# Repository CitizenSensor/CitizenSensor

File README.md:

# CitizenSensor Nitrate Measurement System

This repository contains all design files for the CitizenSensor nitrate measuring system.

## Repository Layout

```
+ 1_RaspberryPi-HAT/            Raspberry Pi HAT allowing electro-chemical measurements
| + Firmware/                   firmware for the ADuCM350 on the HAT
| + Hardware/                   PCB design files for the HAT
+ 2_Software/                   Main software running on the Raspberry Pi
+ 3_Electrometer/               PCB design files for the electrometer amplifier
+ 4_ConnectorBoard/             PCB design files for a small board to connect further components
+ 5_Enclosure/                  3D printable enclosure
+ 6_Accessories/                Additional helpful items
+ README.md                     this readme
```

## Documentation

Documentation can be found in the [CitizenSensor Wiki](https://github.com/CitizenSensor/CitizenSensor/wiki)

## Known Issues

See [Open Issues](https://github.com/CitizenSensor/CitizenSensor/issues?utf8=%E2%9C%93&q=is%3Aopen+is%3Aissue).

## License

The hardware documentation is licensed under CERN OHL v.1.2.

Software is licensed under GPLv3.

For details see licensing info in the respective sub directories.

---

Copyright FabLab München e.V. and Fraunhofer EMFT 2019-2020

CitizenSensor is sponsored by the Federal Ministry of Education and Research

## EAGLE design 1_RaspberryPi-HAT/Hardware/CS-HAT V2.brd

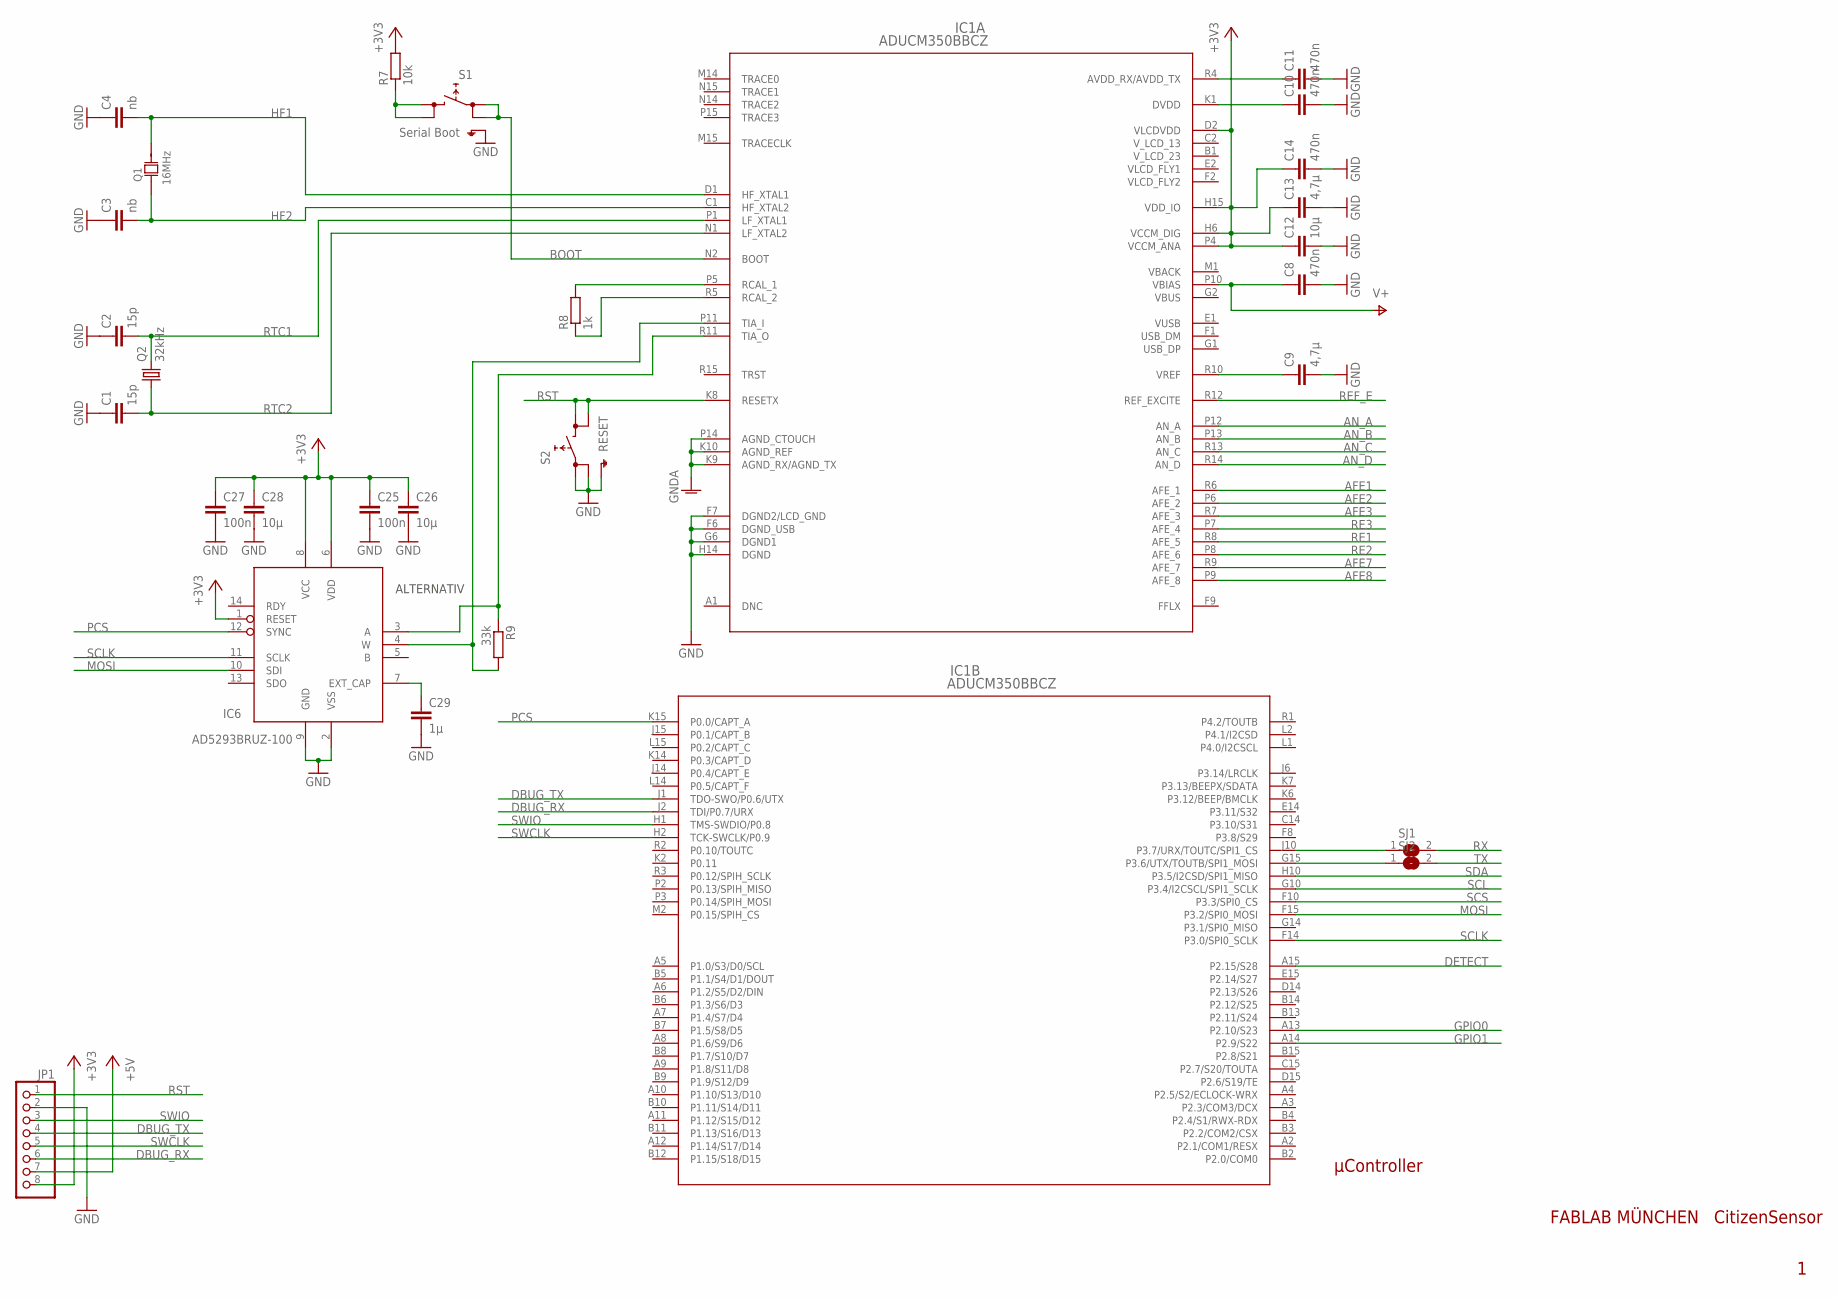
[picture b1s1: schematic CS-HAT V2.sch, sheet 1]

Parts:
C1, C2: 15p; C0805
C3, C4: nb; C0805
C8, C10, C11, C14: 470n; C0805
C9, C13: 4,7µ; C1206
C12, C26, C28: 10µ; C1206
C25, C27: 100n; C0805
C29: 1µ; C1206
IC1: ADUCM350BBCZ; BC_120_3
IC6: AD5293BRUZ-100; TSSOP14
JP1: PINHD-1X8S; 1X08S
Q1: 16MHz; JXS53
Q2: 32kHz; FC-12M
R7: 10k; R0805
R8: 1k; R0805
R9: 33k; R0805
S1: Serial Boot; SKHMPXE010
S2: RESET; SKHMPXE010
SJ1, SJ2: SJ

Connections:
+3V3: C12.1, C13.1, C14.1, C25.1, C26.1, C27.1, C28.1, IC1.D2 (VLCDVDD), IC1.H6 (VCCM_DIG), IC1.H15 (VDD_IO), IC1.P4 (VCCM_ANA), IC6.1 (RESET), IC6.6 (VDD), IC6.8 (VCC), JP1.8, R7.2; also elsewhere on the board
+5V: JP1.7; also elsewhere on the board
AFE1: IC1.R6 (AFE_1); also elsewhere on the board
AFE2: IC1.P6 (AFE_2)
AFE3: IC1.R7 (AFE_3); also elsewhere on the board
AFE7: IC1.R9 (AFE_7); also elsewhere on the board
AFE8: IC1.P9 (AFE_8); also elsewhere on the board
AN_A: IC1.P12 (AN_A); also elsewhere on the board
AN_B: IC1.P13 (AN_B)
AN_C: IC1.R13 (AN_C)
AN_D: IC1.R14 (AN_D); also elsewhere on the board
BOOT: IC1.N2 (BOOT), S1.1 (1.1), S1.2 (1.2); also elsewhere on the board
DBUG_RX: IC1.J2 (TDI/P0.7/URX), JP1.6
DBUG_TX: IC1.J1 (TDO-SWO/P0.6/UTX), JP1.4
DETECT: IC1.A15 (P2.15/S28); also elsewhere on the board
GND: C1.1, C2.1, C3.1, C4.1, C8.2, C9.2, C10.2, C11.2, C12.2, C13.2, C14.2, C25.2, C26.2, C27.2, C28.2, C29.2, IC1.F6 (DGND_USB), IC1.F7 (DGND2/LCD_GND), IC1.G6 (DGND1), IC1.H14 (DGND), IC6.2 (VSS), IC6.9 (GND), JP1.2, S1.5 (SH), S2.1 (1.1), S2.2 (1.2), S2.5 (SH); also elsewhere on the board
GNDA: IC1.K9 (AGND_RX/AGND_TX), IC1.K10 (AGND_REF), IC1.P14 (AGND_CTOUCH); also elsewhere on the board
GPIO0: IC1.A13 (P2.10/S23); also elsewhere on the board
GPIO1: IC1.A14 (P2.9/S22); also elsewhere on the board
HF1: C4.2, IC1.D1 (HF_XTAL1), Q1.3 (2)
HF2: C3.2, IC1.C1 (HF_XTAL2), Q1.1
MOSI: IC1.F15 (P3.2/SPI0_MOSI), IC6.10 (SDI); also elsewhere on the board
unnamed: IC1.J10 (P3.7/URX/TOUTC/SPI1_CS), SJ1.1
unnamed: IC1.G15 (P3.6/UTX/TOUTB/SPI1_MOSI), SJ2.1
unnamed: R7.1, S1.3 (2.1), S1.4 (2.2)
unnamed: C29.1, IC6.7 (EXT_CAP)
unnamed: IC1.P5 (RCAL_1), R8.2
unnamed: IC1.R5 (RCAL_2), R8.1
unnamed: IC1.P11 (TIA_I), IC6.4 (W), R9.2
unnamed: IC1.R11 (TIA_O), IC6.3 (A), R9.1
unnamed: C9.1, IC1.R10 (VREF)
unnamed: C10.1, IC1.K1 (DVDD)
unnamed: C11.1, IC1.R4 (AVDD_RX/AVDD_TX)
PCS: IC1.K15 (P0.0/CAPT_A), IC6.12 (SYNC)
RE1: IC1.R8 (AFE_5); also elsewhere on the board
RE2: IC1.P8 (AFE_6); also elsewhere on the board
RE3: IC1.P7 (AFE_4); also elsewhere on the board
REF_E: IC1.R12 (REF_EXCITE)
RST: IC1.K8 (RESETX), JP1.1, S2.3 (2.1), S2.4 (2.2); also elsewhere on the board
RTC1: C2.2, IC1.P1 (LF_XTAL1), Q2.2
RTC2: C1.2, IC1.N1 (LF_XTAL2), Q2.1
RX: SJ1.2; also elsewhere on the board
SCL: IC1.G10 (P3.4/I2CSCL/SPI1_SCLK); also elsewhere on the board
SCLK: IC1.F14 (P3.0/SPI0_SCLK), IC6.11 (SCLK); also elsewhere on the board
SCS: IC1.F10 (P3.3/SPI0_CS); also elsewhere on the board
SDA: IC1.H10 (P3.5/I2CSD/SPI1_MISO); also elsewhere on the board
SWCLK: IC1.H2 (TCK-SWCLK/P0.9), JP1.5
SWIO: IC1.H1 (TMS-SWDIO/P0.8), JP1.3
TX: SJ2.2; also elsewhere on the board
V+: C8.1, IC1.P10 (VBIAS); also elsewhere on the board

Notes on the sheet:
FABLAB MÜNCHEN CitizenSensor
µController
ALTERNATIV

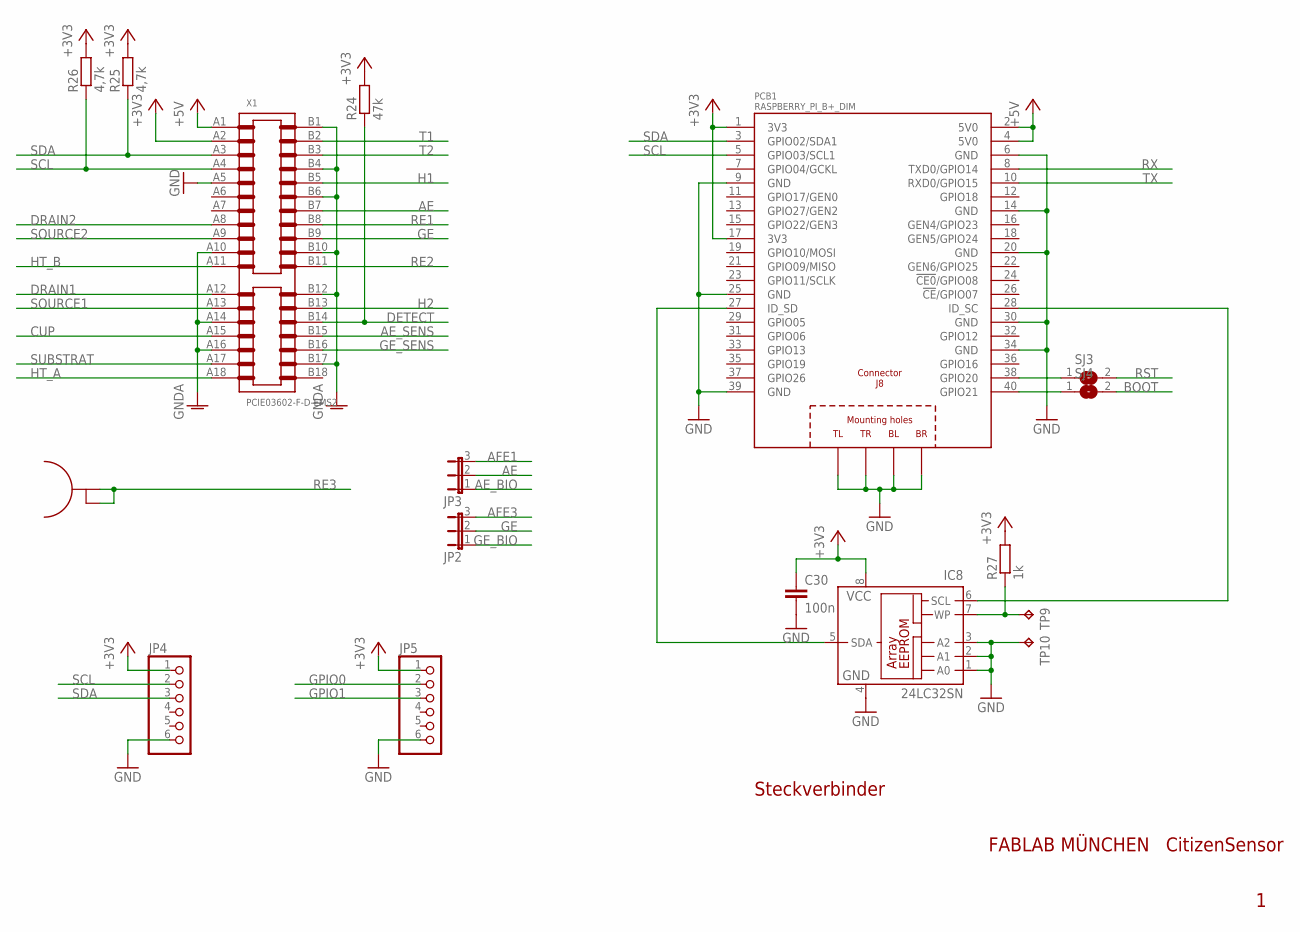
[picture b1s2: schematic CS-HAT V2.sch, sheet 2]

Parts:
C30: 100n; C0805
IC8: 24LC32SN; SO-08
JP2, JP3: JP2ES; JP2S
JP4, JP5: PINHD-1X6S; 1X06S
PCB1: RASPBERRY_PI_B+_DIM; RASPBERRY_PI_BPLUS_DIM
R24: 47k; R0805
R25, R26: 4,7k; R0805
R27: 1k; R0805
SJ3, SJ4: SJ
TP8: TESTPLUG2MM
TP9, TP10: TPB2,54; B2,54
X1: PCIE03602-F-D-EMS2; PCIE-036-02-F-D-EMS2

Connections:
+3V3: C30.1, IC8.8 (VCC), JP4.1, JP5.1, PCB1.1 (3V3), PCB1.17 (3V3), R24.2, R25.2, R26.2, R27.2, X1.A2; also elsewhere on the board
+5V: PCB1.2 (5V0), PCB1.4 (5V0), X1.A1; also elsewhere on the board
AE: JP3.2, X1.B7
AE_BIO: JP3.1; also elsewhere on the board
AE_SENS: X1.B15; also elsewhere on the board
AFE1: JP3.3; also elsewhere on the board
AFE3: JP2.3; also elsewhere on the board
BOOT: SJ4.2; also elsewhere on the board
CUP: X1.A15
DETECT: R24.1, X1.B14; also elsewhere on the board
DRAIN1: X1.A12
DRAIN2: X1.A8
GE: JP2.2, X1.B9
GE_BIO: JP2.1; also elsewhere on the board
GE_SENS: X1.B16; also elsewhere on the board
GND: C30.2, IC8.1 (A0), IC8.2 (A1), IC8.3 (A2), IC8.4 (GND), JP4.6, JP5.6, PCB1.6 (GND), PCB1.9 (GND), PCB1.14 (GND), PCB1.20 (GND), PCB1.25 (GND), PCB1.30 (GND), PCB1.34 (GND), PCB1.39 (GND), PCB1.PE_BL (BL), PCB1.PE_BR (BR), PCB1.PE_TL (TL), PCB1.PE_TR (TR), TP10.TP, X1.A5; also elsewhere on the board
GNDA: X1.A10, X1.A14, X1.A16, X1.B1, X1.B4, X1.B6, X1.B10, X1.B12, X1.B17; also elsewhere on the board
GPIO0: JP5.2; also elsewhere on the board
GPIO1: JP5.3; also elsewhere on the board
H1: X1.B5; also elsewhere on the board
H2: X1.B13
HT_A: X1.A18
HT_B: X1.A11
unnamed: PCB1.40 (GPIO21), SJ4.1
unnamed: PCB1.38 (GPIO20), SJ3.1
unnamed: IC8.5 (SDA), PCB1.27 (ID_SD)
unnamed: IC8.6 (SCL), PCB1.28 (ID_SC)
unnamed: IC8.7 (WP), R27.1, TP9.TP
RE1: X1.B8; also elsewhere on the board
RE2: X1.B11; also elsewhere on the board
RE3: TP8.A, TP8.B; also elsewhere on the board
RST: SJ3.2; also elsewhere on the board
RX: PCB1.8 (TXD0/GPIO14); also elsewhere on the board
SCL: JP4.2, PCB1.5 (GPIO03/SCL1), R26.1, X1.A4; also elsewhere on the board
SDA: JP4.3, PCB1.3 (GPIO02/SDA1), R25.1, X1.A3; also elsewhere on the board
SOURCE1: X1.A13
SOURCE2: X1.A9
SUBSTRAT: X1.A17
T1: X1.B2; also elsewhere on the board
T2: X1.B3; also elsewhere on the board
TX: PCB1.10 (RXD0/GPIO15); also elsewhere on the board

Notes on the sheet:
FABLAB MÜNCHEN CitizenSensor
Steckverbinder

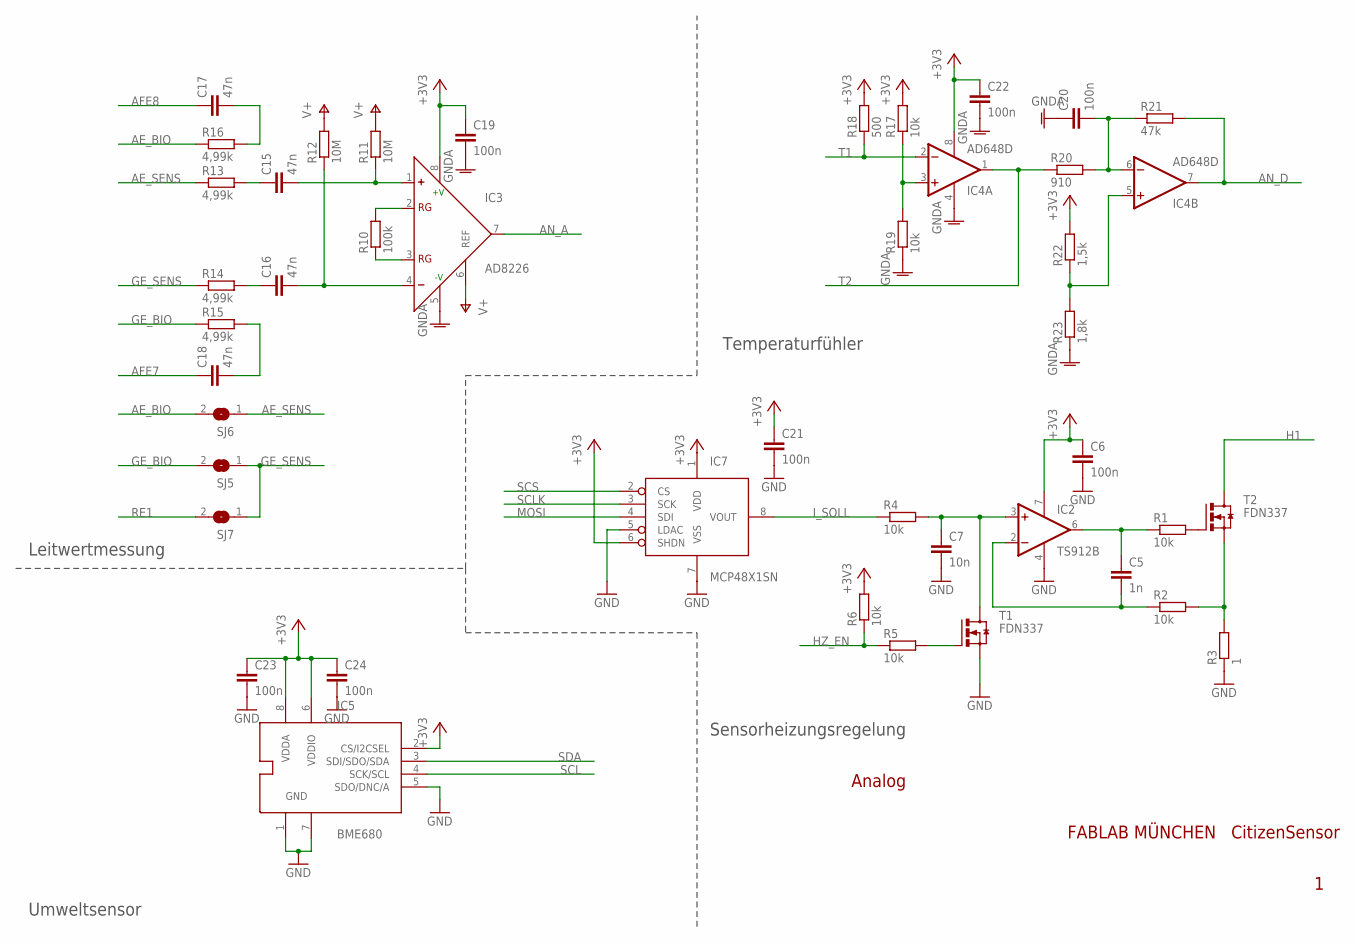
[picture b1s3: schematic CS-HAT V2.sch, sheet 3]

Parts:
C5: 1n; C0805
C6, C19, C20, C21, C22, C23, C24: 100n; C0805
C7: 10n; C0805
C15, C16, C17, C18: 47n; C0805
IC2: TS912B; SO08
IC3: AD8226; SO8
IC4: AD648D; SO08
IC5: BME680
IC7: MCP48X1SN; SO-08
R1, R2, R4, R5, R6, R17, R19: 10k; R0805
R3: 1; R1210
R10: 100k; R0805
R11, R12: 10M; R0805
R13, R14, R15, R16: 4,99k; R0805
R18: 500; R0805
R20: 910; R0805
R21: 47k; R0805
R22: 1,5k; R0805
R23: 1,8k; R0805
SJ5, SJ6, SJ7: SJ
T1, T2: FDN337; SUPER-SOT3

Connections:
+3V3: C6.1, C19.1, C21.1, C22.1, C23.1, C24.1, IC2.7 (V+), IC3.8 (+V), IC4.8 (V+), IC5.2 (CS/I2CSEL), IC5.6 (VDDIO), IC5.8 (VDDA), IC7.1 (VDD), IC7.6 (SHDN), R6.2, R17.2, R18.2, R22.2; also elsewhere on the board
AE_BIO: R16.1, SJ6.2; also elsewhere on the board
AE_SENS: R13.1, SJ6.1; also elsewhere on the board
AFE7: C18.1; also elsewhere on the board
AFE8: C17.1; also elsewhere on the board
AN_A: IC3.7 (OUT); also elsewhere on the board
AN_D: IC4.7 (OUT), R21.2; also elsewhere on the board
GE_BIO: R15.1, SJ5.2; also elsewhere on the board
GE_SENS: R14.1, SJ5.1, SJ7.1; also elsewhere on the board
GND: C6.2, C7.2, C21.2, C23.2, C24.2, IC2.4 (V-), IC5.1 (GND), IC5.5 (SDO/DNC/A), IC5.7 (GND), IC7.5 (LDAC), IC7.7 (VSS), R3.1, T1.2 (S); also elsewhere on the board
GNDA: C19.2, C20.1, C22.2, IC3.5 (-V), IC4.4 (V-), R19.1, R23.1; also elsewhere on the board
H1: T2.3 (D); also elsewhere on the board
HZ_EN: R5.1, R6.1
I_SOLL: IC7.8 (VOUT), R4.1
MOSI: IC7.4 (SDI); also elsewhere on the board
unnamed: C5.1, IC2.6 (OUT), R1.1
unnamed: C5.2, IC2.2 (-IN), R2.1
unnamed: R1.2, T2.1 (G)
unnamed: R2.2, R3.2, T2.2 (S)
unnamed: C7.1, IC2.3 (+IN), R4.2, T1.3 (D)
unnamed: R5.2, T1.1 (G)
unnamed: IC3.2 (RG), R10.2
unnamed: C18.2, R15.2
unnamed: IC3.3 (RG), R10.1
unnamed: C15.2, IC3.1 (+), R11.1
unnamed: C16.2, IC3.4 (-), R12.1
unnamed: C16.1, R14.2
unnamed: C15.1, R13.2
unnamed: C17.2, R16.2
unnamed: IC4.3 (+IN), R17.1, R19.2
unnamed: C20.2, IC4.6 (-IN), R20.2, R21.1
unnamed: IC4.5 (+IN), R22.1, R23.2
RE1: SJ7.2; also elsewhere on the board
SCL: IC5.4 (SCK/SCL); also elsewhere on the board
SCLK: IC7.3 (SCK); also elsewhere on the board
SCS: IC7.2 (CS); also elsewhere on the board
SDA: IC5.3 (SDI/SDO/SDA); also elsewhere on the board
T1: IC4.2 (-IN), R18.1; also elsewhere on the board
T2: IC4.1 (OUT), R20.1; also elsewhere on the board
V+: IC3.6 (REF), R11.2, R12.2; also elsewhere on the board

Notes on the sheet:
FABLAB MÜNCHEN CitizenSensor
Analog
Leitwertmessung
Umweltsensor
Sensorheizungsregelung
Temperaturfühler

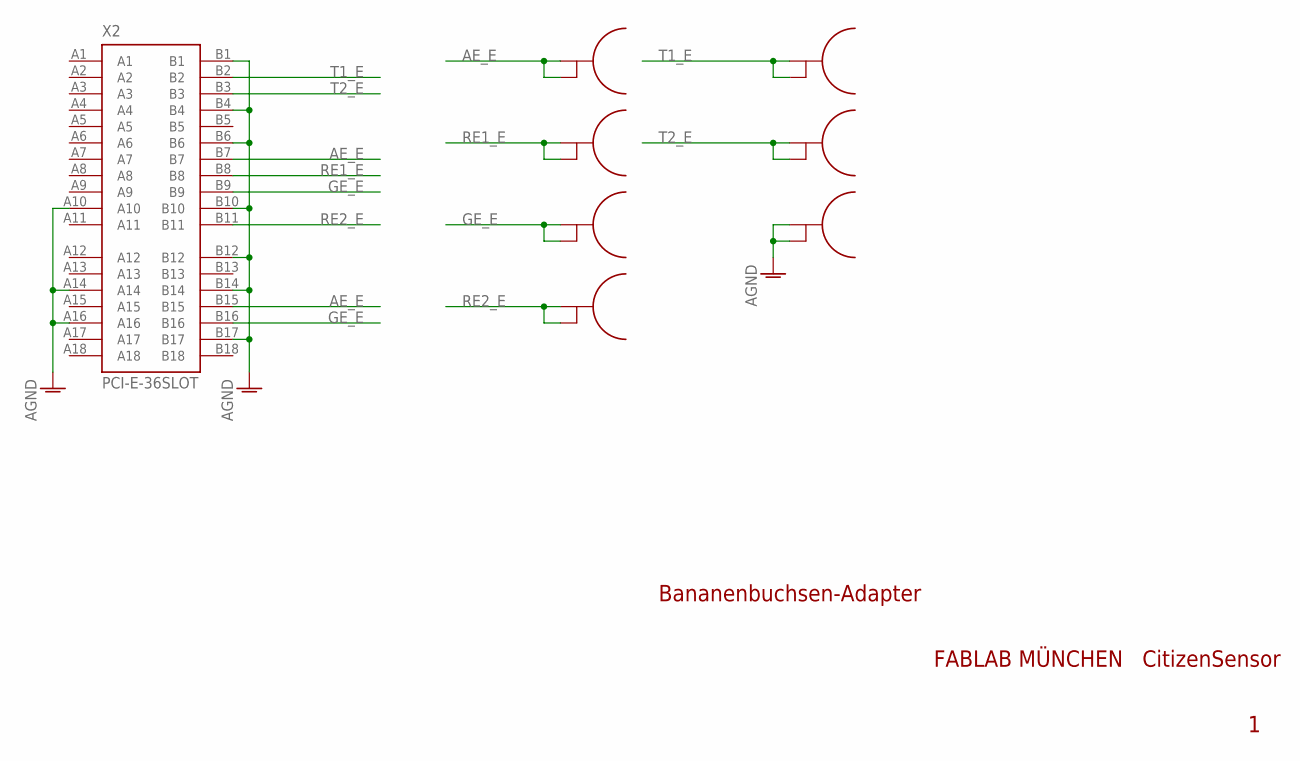
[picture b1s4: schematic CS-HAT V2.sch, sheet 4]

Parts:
TP1, TP2, TP3, TP4, TP5, TP6, TP7: TESTPLUG2MM
X2: PCI-E-36SLOT; PCI-E-36_SLOT

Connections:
AE_E: TP1.A, TP1.B, X2.B7, X2.B15
AGND: TP7.A, TP7.B, X2.A10, X2.A14, X2.A16, X2.B1, X2.B4, X2.B6, X2.B10, X2.B12, X2.B14, X2.B17
GE_E: TP3.A, TP3.B, X2.B9, X2.B16
RE1_E: TP2.A, TP2.B, X2.B8
RE2_E: TP4.A, TP4.B, X2.B11
T1_E: TP5.A, TP5.B, X2.B2
T2_E: TP6.A, TP6.B, X2.B3

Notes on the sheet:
FABLAB MÜNCHEN CitizenSensor
Bananenbuchsen-Adapter

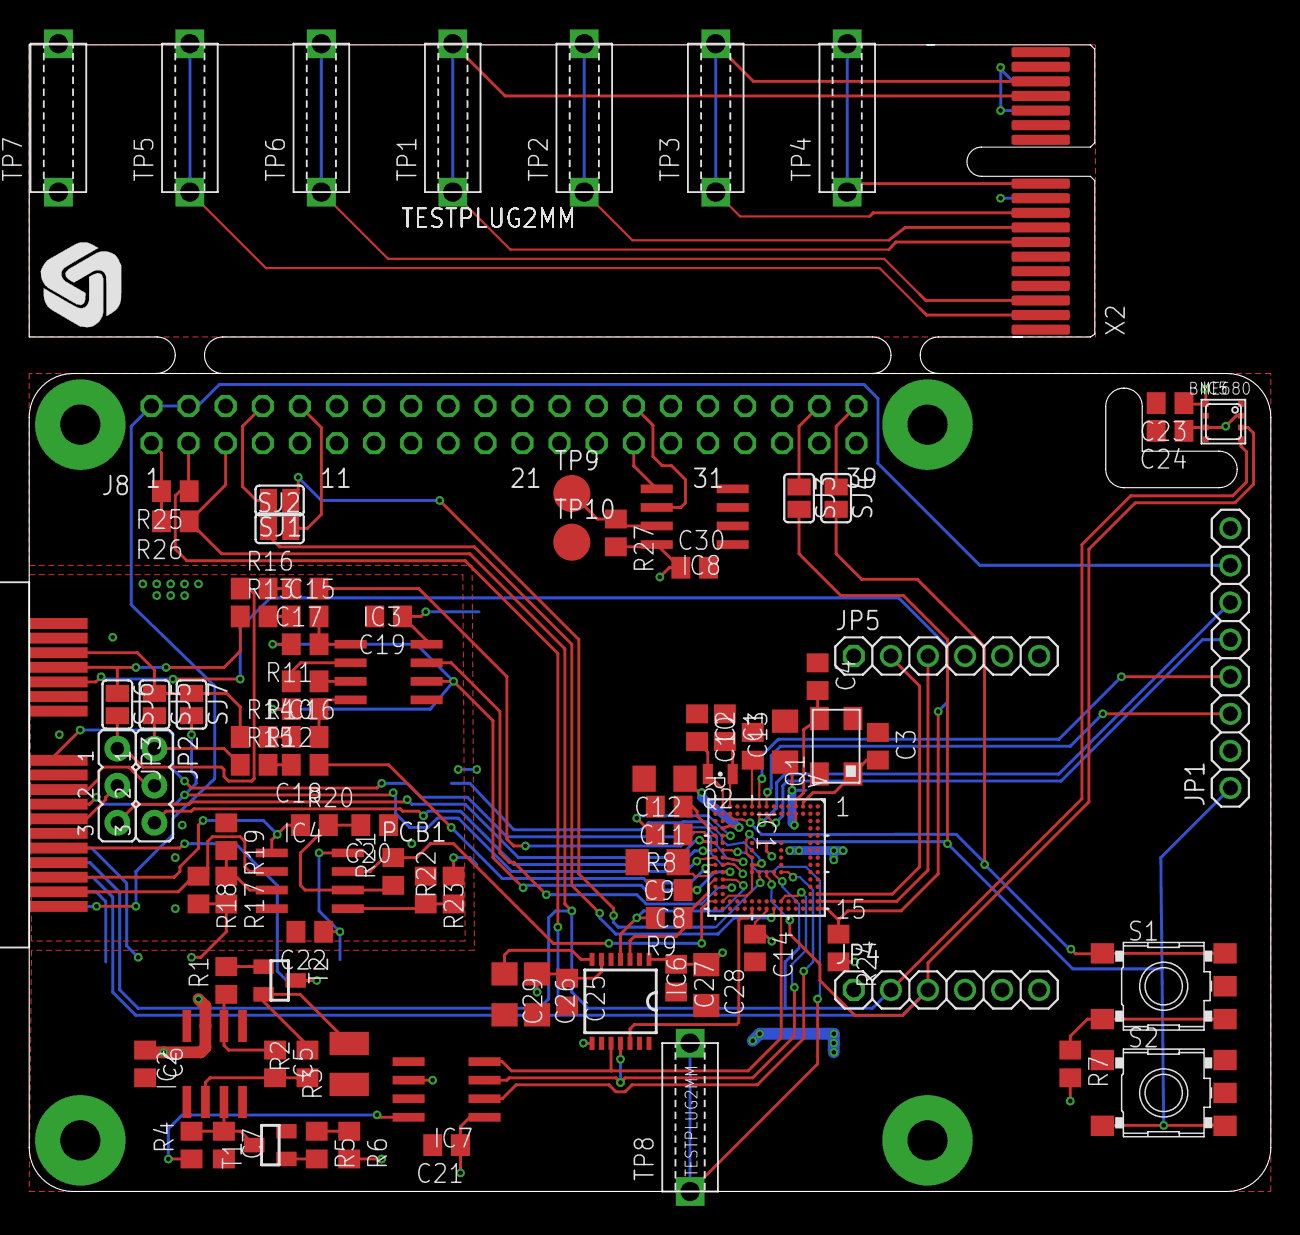
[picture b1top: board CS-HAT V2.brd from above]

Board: 2 copper layers, 85.0 x 78.5 mm, 96 parts (0 on the bottom side), 86 nets.

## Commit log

2019-10-30 initial commit, setting up directory structure
2019-10-30 added link to Wiki
2019-10-30 added connector board rev 2.0
2019-10-30 added enclosure stl files rev 2.0
2019-11-03 link to photo in wiki
2020-01-27 added pi software v200127
2020-01-27 updated license information
2020-01-27 add firmware for the Pi HAT v200127
2020-02-16 Create _Footer.md
    Initial commit
2020-02-16 Commit for first pull request
2020-02-16 Added soil sampling images, fixed links
2020-02-16 Fixed link to english article
2020-02-16 Fixed link to german article
2020-02-16 Fixed invalid link
2020-02-16 Add GPIO Connector Board overview, BOM and instructions to documentation #13
2020-02-16 fix table
2020-02-19 added enclosure STEP files
2020-02-19 added BOM
2020-02-24 added GerberFiles
2020-02-24 added qr code for düngebroschüre and added reset of HAT
2020-02-24 fixed path to main.py
2020-02-24 fixed spacings and database filename
2020-02-26 bug fixes
2020-02-26 changed qr resolution
2020-02-28 Added soil preparation images
2020-02-28 Added blank image
2020-02-28 First push of soil preparation documentation
2020-02-28 Fixed broken links between DE/EN docu
2020-02-28 Fixed broken links (part 2)
2020-03-01 Added further documentation content
2020-03-01 Fixed links
2020-03-01 Fixed link
2020-03-02 Added nitrate electrode
2020-03-02 added URL to datasheet of Nitrate electrode
2020-03-02 excerpt for dividing by zero at measurement routine
2020-03-04 added missing items to bom
2020-03-05 Added weight
2020-03-05 Changed cup amount to 5
    ISA, Calibration stock solution, calibration 4 ppm, calibration 100 ppm, sample solution
2020-03-05 fixed typo
2020-03-06 added cup_cap to 6_Accessories
2020-03-06 fixed hole dia
2020-03-07 Added new images
2020-03-07 Linked new images. Improved one image name.
2020-03-08 3 bilder von matthias (gerät offen)
2020-03-19 Added OpenSource information
2020-03-21 Updated OSS information
2020-04-07 separated ADI code and Citizensensor code
2020-04-07 Added soil sampling/preparation images
2020-04-07 Linked soil sampling/preparation images
2020-04-19 Added image: Bodenmühle
2020-05-02 Added Eagle files
2020-05-02 Add BOM
2020-07-06 main change
2020-07-09 changed ppm label to .2f float format
2020-07-18 Added localized Wiki texts (EN)
2020-07-18 Added localized texts - part 2
2020-07-25 Images for Aqueous Solution
2020-07-25 Documentation Aqueous Solution
2020-08-03 CS Orbital Shaker Initial Commit
2020-08-03 CS Orbital Shaker Readme edit
2020-10-21 Added assembly Wiki pages.
2020-10-21 Removed superfluous text.
2020-12-17 added fusion source files for enclosure
2022-02-09 changed averaging factor for scale to uneven number
2022-02-09 change weighing average factor to uneven number
2022-02-14 Update bom.md
    New ebay Links for plastic cups
2022-02-14 More detail on plastic cups
2022-02-15 changed some steps
